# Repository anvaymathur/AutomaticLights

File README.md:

# AutomaticLights

This is a system to automatically turn on your RGB strip lights, using LD2410C motion sensors for presence detection,
and a BH105 light sensor for changing brightness based on ambient lighting. 

## Description

This system was built due to my room's lack of RGB strip lighting. I have always wanted some but I never had any,
and I also never bought any because I dind't want the hassle of turning them on and off all the time. And keeping them on
all the time would draw too much electricity. So I wanted to build a system where the lights will turn on and off based on if I
am at my desk or in the room. This makes it really easy to maintain and make sure it is not drawing too much power.

## Features

* 3D Printed Case
* RGB Strip Lights
* Presence Detection using a LD2410C sensor
* Ambient Lighting detection using a BH105 sensor
* USB - C Powered and USB - C programmable
* Hand wired

## Schematic

Since the project is hand wired there is no real need for a schematic but I decided to make one anyway to make it easy to keep track
of what components connect to what, and approximately where each component will be (done with the layout and routing in the PCB editor of KiCad). I plan to use a perfboard to connect everything together. Some symbols and footprints were used from SnapMagic.

## CAD

Custom 3D Printable case which houses all of the electronics for the project other than the RGB lightstrip itself. It has a base, which
houses the main perfboard, the USB-C breakout board, the BH105 sensor and the LD2410C sensor. Each sensor and the breakout board
has certain slots to fit into to keep them in the right spot, so that they stay consistent and don't move around if the box is moved.
It also has the holes for the power USB-C, the RGB light strip's wires, and the programming USB-C and MicroUSB ports. Make sure to never
plug a USB into the programming ports if it is also recieving power from the power port. For the lid, it is attached to the case using M2 
screws with M2 screw's threaded inserts. 

## Firmware

The firmware currently can control the RGB lights based on if the LD2410C sensor detects anything. It also adjusts the brightness of the 
lights based on the ambient lighting detected by the BH105 sensor. I will also later add ability to control my room's lights based
on if I enter the room, and adjust the different colors and flows of the LED light strip. It can be found in the firmware folder, the code.py
file should be uploaded to the ESP32 which should already be flashed with circuit python. I would reccomend for autocomplete and to get
the correct libraries for offline development without an ESP32, use the .venv python interpreter in VSCode to be able to have a proper autocomplete and not be riddled with warnings and errors. For the best experience make sure VSCode has the firmware folder itself open
otherwise it will not detect the additional library used in the lib folder under the firmware folder.   

## Bill Of Materials (BOM)

| Item | Description | Preowned | # of Sets | # Pcs / Set | Price / Set (USD) | Item Total Price + Tax & Shipping (USD) | Supplier | URL|
| :--  | :---------- | :------- | :-------- | :---------- | :---------------- | :-------------------------------------- | :------- |:-- |
| ESP32-S3-DevKitC-1 | Microcontroller | NO | 1 | 1 | $6.41 | *$6.41* | Aliexpress | https://www.aliexpress.com/item/1005006429853362.html|
| HLK-LD2410C 24G    | Motion sensor   | NO | 1 | 1 | $3.75 | *$3.75* | Aliexpress | https://www.aliexpress.com/item/1005005629674638.html |
| SN74AHCT125N       | Level Shifter   | NO | 1 | 1 | $2.07 | *$2.07* | Aliexpress | https://www.aliexpress.com/item/1005007655828920.html |
| GY-302 BH1750      | Light Sensor    | NO | 1 | 1	| $1.90	| *$1.90* | Aliexpress | https://www.aliexpress.com/item/1005010446317363.html |
| Glass Fuse Holder 22 AWG with 4A Glass Fuse | Fuse Holder & Fuse | NO | 1	| 5	| $2.74	| *$2.74* | Aliexpress | https://www.aliexpress.com/item/1005007846817140.html |
| Terminal Block Connector Pitch 5.0mm - 2P Green | Screw Terminal | NO | 1	| 10 | $1.84 | *$1.84* | Aliexpress | https://www.aliexpress.com/item/1005007055503766.html |
| Aluminum Electrolytic Capacitor 10V 1000UF | Capacitor | NO | 1 | 20 | $3.93 | *$3.93* | Aliexpress | https://www.aliexpress.com/item/1005011811368397.html |
| Metal Film Resistors - 330Ω | Resistors | YES | 1 | 100 | $3.79 | *$3.79* | Aliexpress | https://www.aliexpress.com/item/1005003021542565.html |
| USB-C Breakout Board | Power | YES | 1 | 1 | $1.13 | *$1.13* | Aliexpress | https://www.aliexpress.com/item/1005004848153846.html |
| WS2812B RGBIC Smart LED Strip - IP30 60 LEDS 2m | LED Strip | NO | 1 | 1 | $7.11 | $7.11 | Aliexpress | https://www.aliexpress.com/item/1005009135730524.html |
| **Grand Total (USD)** | | | | | | *$34.67* | | |
| **Grand Total New (USD)** | | | | | | *$29.75* | | |

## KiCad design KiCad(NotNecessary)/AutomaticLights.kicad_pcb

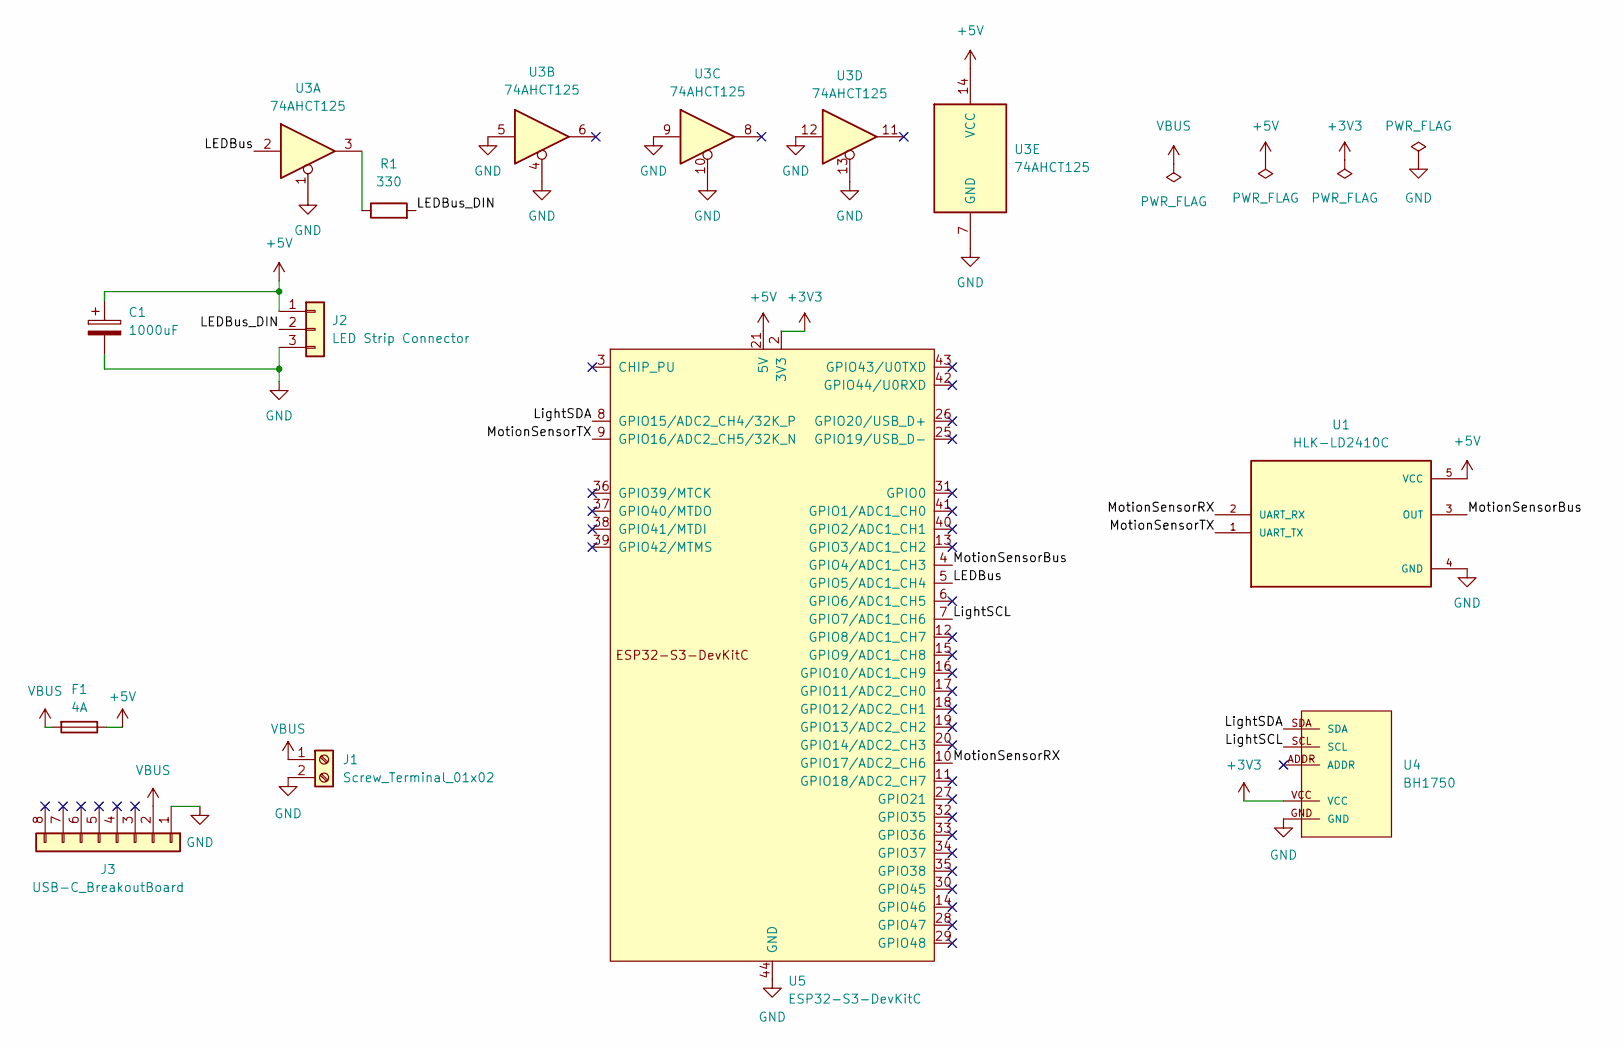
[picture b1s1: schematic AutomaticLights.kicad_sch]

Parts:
C1: 1000uF; CP_Radial_D8.0mm_P5.00mm
F1: 4A; PinHeader_1x02_P2.54mm_Vertical
J1: Screw_Terminal_01x02; TerminalBlock_Phoenix_MKDS-1,5-2-5.08_1x02_P5.08mm_Horizont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
J2: LED Strip Connector; PinHeader_1x03_P2.54mm_Vertical
J3: USB-C_BreakoutBoard; PinHeader_1x08_P2.54mm_Vertical
R1: 330; R_Axial_DIN0207_L6.3mm_D2.5mm_P10.16mm_Horizontal
U1: HLK-LD2410C; MODULE_HLK-LD2410C; PARTREV V1.00
U3: 74AHCT125; DIP-14_W7.62mm
U4: BH1750; ZC362800_
U5: ESP32-S3-DevKitC

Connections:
+3V3: U4.VCC, U5.1 (3V3), U5.2 (3V3)
+5V: C1.1, F1.1, J2.1 (VCC), U1.5 (VCC), U3.14 (VCC), U5.21 (5V)
/LEDBus: U3.2, U5.5 (GPIO5/ADC1_CH4)
/LEDBus_DIN: J2.2 (DIN), R1.2
/LightSCL: U4.SCL, U5.7 (GPIO7/ADC1_CH6)
/LightSDA: U4.SDA, U5.8 (GPIO15/ADC2_CH4/32K_P)
/MotionSensorBus: U1.3 (OUT), U5.4 (GPIO4/ADC1_CH3)
/MotionSensorRX: U1.2 (UART_RX), U5.10 (GPIO17/ADC2_CH6)
/MotionSensorTX: U1.1 (UART_TX), U5.9 (GPIO16/ADC2_CH5/32K_N)
GND: C1.2, J1.2, J2.3 (GND), J3.1, U1.4 (GND), U3.1, U3.4, U3.5, U3.7 (GND), U3.9, U3.10, U3.12, U3.13, U4.GND, U5.22 (GND), U5.23 (GND), U5.24 (GND), U5.44 (GND)
unnamed: R1.1, U3.3
VBUS: F1.2, J1.1, J3.2

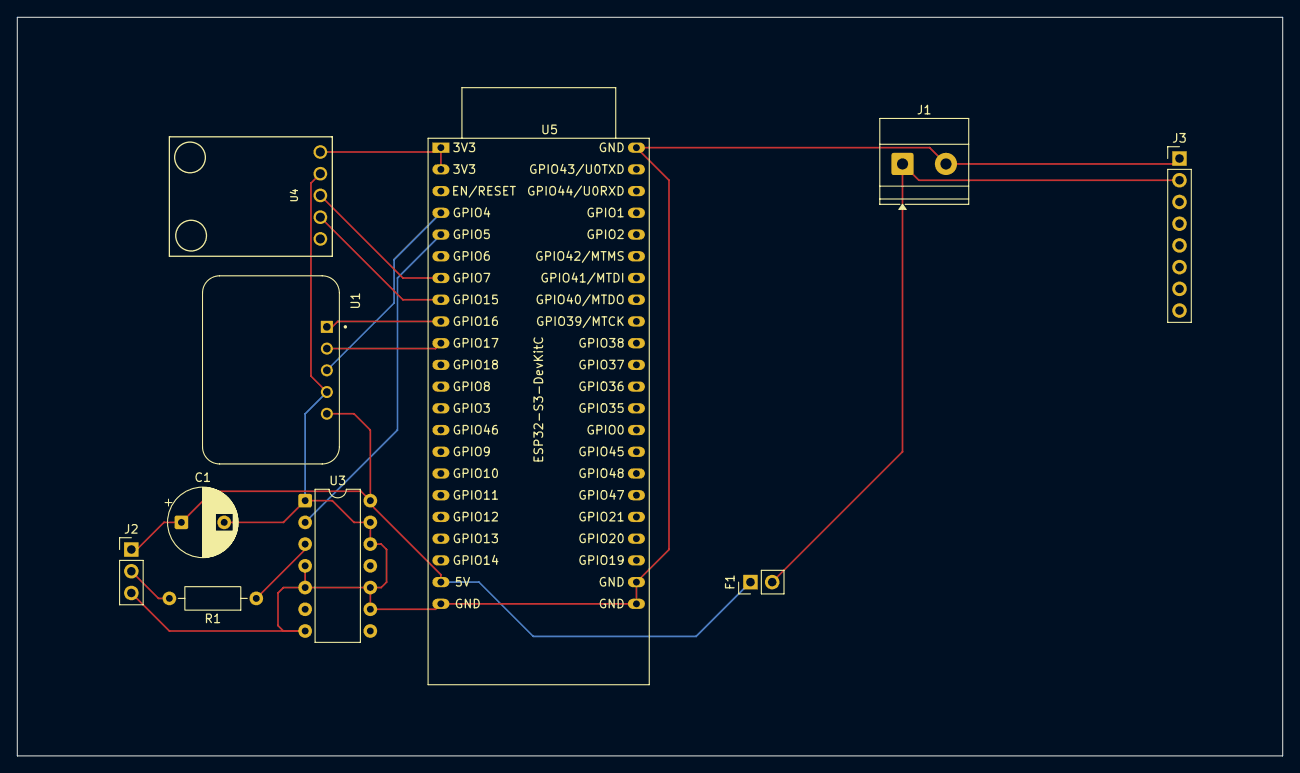
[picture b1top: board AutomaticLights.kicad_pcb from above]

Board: 2 copper layers, 148.0 x 86.4 mm, 10 parts (0 on the bottom side), 12 nets.

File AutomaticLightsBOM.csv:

Item,Description,Preowned ,# of Sets,#Pcs / Set,Price/Set (USD),Item Total Price + Tax & Shipping (USD),Supplier,URL
ESP32-S3-DevKitC-1,Microcontroller,NO,1,1,$6.41,$6.41,Aliexpress,https://www.aliexpress.com/item/1005006429853362.html
HLK-LD2410C 24G,Motion sensor,NO,1,1,$3.75,$3.75,Aliexpress,https://www.aliexpress.com/item/1005005629674638.html
SN74AHCT125N,Level Shifter,NO,1,1,$2.07,$2.07,Aliexpress,https://www.aliexpress.com/item/1005007655828920.html
GY-302 BH1750,Light Sensor,NO,1,1,$1.90,$1.90,Aliexpress,https://www.aliexpress.com/item/1005010446317363.html
Glass Fuse Holder 22 AWG with 4A Glass Fuse,Fuse Holder & Fuse,NO,1,5,$2.74,$2.74,Aliexpress,https://www.aliexpress.com/item/1005007846817140.html
Terminal Block Connector Pitch 5.0mm - 2P Green,Screw Terminal,NO,1,10,$1.84,$1.84,Aliexpress,https://www.aliexpress.com/item/1005007055503766.html
Aluminum Electrolytic Capacitor 10V 1000UF,Capacitor,NO,1,20,$3.93,$3.93,Aliexpress,https://www.aliexpress.com/item/1005011811368397.html
Metal Film Resistors 330Ω,Resistors,YES,1,100,$3.79,$3.79,Aliexpress,https://www.aliexpress.com/item/1005003021542565.html
USB C Breakout Board,For Power,YES,1,1,$1.13,$1.13,Aliexpress,https://www.aliexpress.com/item/1005004848153846.html
WS2812B RGBIC Smart LED Strip - IP 30 60 LEDS 2m,LED Strip,NO,1,1,$7.11,$7.11,Aliexpress,https://www.aliexpress.com/item/1005009135730524.html
Grand Total (USD),,,,,,$34.67,,
,,,,,,,,
Grand Total New (USD),,,,,,$29.75,,

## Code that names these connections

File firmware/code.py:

# Presence light: turns the LED strip on when the radar sees someone
# and the room is dark, and fades it off when they leave.
#
# Wiring (from the schematic):
#   GPIO5  -> level shifter -> 330 ohm -> LED strip DIN
#   GPIO17 -> radar RX   (ESP32 sends)
#   GPIO16 <- radar TX   (ESP32 receives)
#   GPIO7  -> light sensor SCL
#   GPIO15 -> light sensor SDA

import time
import board
import busio
import neopixel
import adafruit_bh1750
import mmwave_presence as mmwave

# ---------------- settings: change these ----------------
NUM_LEDS = 120          # 2 m x 60 LEDs per metre
COLOR = (255, 180, 100) # warm white
MAX_BRIGHTNESS = 0.35    # 0 to 1. Keep at 0.4 or below: 120 warm-white LEDs at
                        # full brightness would pull about 5 A, more than the 3 A charger
DARK_LUX = 20           # room counts as dark below this many lux
HOLD_SECONDS = 30       # radar keeps reporting "someone here" this long after you vanish
FADE_SECONDS = 2.0      # time to fade fully on or off

pixels = neopixel.NeoPixel(board.IO5, NUM_LEDS, brightness=0, auto_write=False, pixel_order=neopixel.GRB)
pixels.fill(COLOR)
pixels.show()

i2c = busio.I2C(board.IO7, board.IO15)
light_sensor = adafruit_bh1750.BH1750(i2c)

uart = busio.UART(board.IO17, board.IO16, baudrate=mmwave.DEFAULT_BAUD, timeout=0.1)
radar = mmwave.MMWave(uart, engineering_always=False)

radar.set_basic_config(8, 8, HOLD_SECONDS)
print("Radar ready, presence timeout:", radar.presence_timeout, "s")

lights_on = False
brightness = 0.0
last_time = time.monotonic()

while True:
    radar.read()                 
    someone_here = radar.detected
    lux = light_sensor.lux

    if not lights_on and someone_here and lux < DARK_LUX:
        lights_on = True
    elif lights_on and not someone_here:
        lights_on = False

    now = time.monotonic()
    step = (now - last_time) / FADE_SECONDS * MAX_BRIGHTNESS
    last_time = now
    target = MAX_BRIGHTNESS if lights_on else 0.0
    if brightness < target:
        brightness = min(target, brightness + step)
    elif brightness > target:
        brightness = max(target, brightness - step)

    pixels.brightness = brightness
    pixels.show()

    print("someone:", someone_here, "distance:", radar.detection_cm, "cm",
          "lux:", round(lux), "lights:", lights_on, "brightness:", round(brightness, 2))
